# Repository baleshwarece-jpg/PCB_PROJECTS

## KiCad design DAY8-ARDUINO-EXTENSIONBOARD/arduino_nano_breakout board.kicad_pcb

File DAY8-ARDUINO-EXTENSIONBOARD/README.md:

# Arduino Nano Extension Board

### Compact GPIO breakout and prototyping platform for Arduino Nano development

---

## Overview

The Arduino Nano Extension Board is a simple yet highly practical PCB designed to transform the Arduino Nano into a more accessible and organized development platform. Rather than connecting sensors and modules directly to the Nano's tightly packed headers, this board expands every I/O pin into clearly labeled breakout connections, simplifying wiring, debugging, and rapid prototyping.

Designed in KiCad, the board emphasizes usability, signal accessibility, and clean PCB design practices while serving as a reusable hardware platform for embedded systems development.

---

## How It Works

The Arduino Nano plugs into a pair of female header sockets located at the center of the PCB. Every microcontroller pin is routed to dedicated breakout headers, allowing external peripherals to be connected without directly interacting with the Nano module.

Power rails distribute 5V and GND throughout the board, providing convenient access points for sensors, actuators, communication modules, and experimental circuits.

The extension board itself contains no active processing circuitry; instead, it functions as a structured interface layer between the Arduino Nano and external hardware, reducing wiring complexity and improving development efficiency.

---

## Bill of Materials

| Reference | Value          | Description                        | KiCad Symbol                | Footprint          |
| --------- | -------------- | ---------------------------------- | --------------------------- | ------------------ |
| U1        | Arduino Nano   | Microcontroller development module | MCU_Module:Arduino_Nano     | Pin Socket Headers |
| J1-Jn     | Pin Headers    | GPIO breakout connectors           | Connector_Generic:Conn_01xN | PinHeader_2.54mm   |
| C1        | 100 nF         | Power supply decoupling capacitor  | Device:C                    | C_0805             |
| H1-H4     | Mounting Holes | Mechanical mounting points         | Mechanical:MountingHole     | MountingHole_3.2mm |

Component count may vary depending on header configuration and optional features.

---

## Electrical Specifications

| Parameter                | Value                  |
| ------------------------ | ---------------------- |
| Operating Voltage        | 5 V                    |
| Logic Voltage            | 5 V                    |
| Input Power Source       | Arduino Nano USB / VIN |
| GPIO Access              | All Nano I/O Pins      |
| Analog Inputs            | A0 – A7                |
| Digital Inputs/Outputs   | D0 – D13               |
| Communication Interfaces | UART, SPI, I²C         |
| PCB Type                 | Two-Layer FR4          |
| Header Pitch             | 2.54 mm                |

---

## Schematic

Designed in KiCad 7.

Repository contents include:

* **Schematic:** `hardware/arduino_nano_extension.kicad_sch`
* **PCB Layout:** `hardware/arduino_nano_extension.kicad_pcb`
* **Gerber Files:** `hardware/gerbers/`
* **BOM:** `hardware/bom.csv`

The design passes ERC validation and follows standard Arduino Nano pin mapping conventions.

---

## Design Notes

### Why an Extension Board?

Although the Arduino Nano is one of the most widely used development boards, direct wiring often becomes difficult when multiple sensors, displays, and communication modules are connected simultaneously. An extension board provides a structured interface that improves accessibility and reduces connection errors.

### Header-Based Expansion

Every Nano pin is routed to dedicated headers, allowing peripherals to be connected without stacking wires directly onto the microcontroller module. This approach improves maintainability and makes debugging significantly easier.

### Power Distribution

Dedicated 5V and GND rails are distributed throughout the PCB to minimize wiring clutter during prototyping. Wide power traces were used to improve current handling and reduce voltage drop when powering multiple peripherals.

### Reusability

The board was designed as a general-purpose development platform rather than a project-specific shield. This allows the same PCB to be reused across robotics, IoT, automation, and embedded systems projects.

---

## Getting Started

1. Open the project files using KiCad 7 or later.
2. Review the schematic and verify ERC results.
3. Generate fabrication files or use the supplied Gerbers.
4. Assemble headers and passive components.
5. Install an Arduino Nano into the designated sockets.
6. Connect sensors, actuators, or communication modules through the breakout headers.
7. Upload firmware to the Nano and begin development.

No firmware modifications are required for board operation.

---

## License

Released under the CERN Open Hardware Licence Version 2 – Permissive (CERN-OHL-P).
You are free to study, modify, manufacture, and distribute this design in accordance with the license terms.

---

## References

* Arduino Nano Technical Documentation
* KiCad EDA Documentation
* Atmel ATmega328P Datasheet
* CERN Open Hardware Licence v2

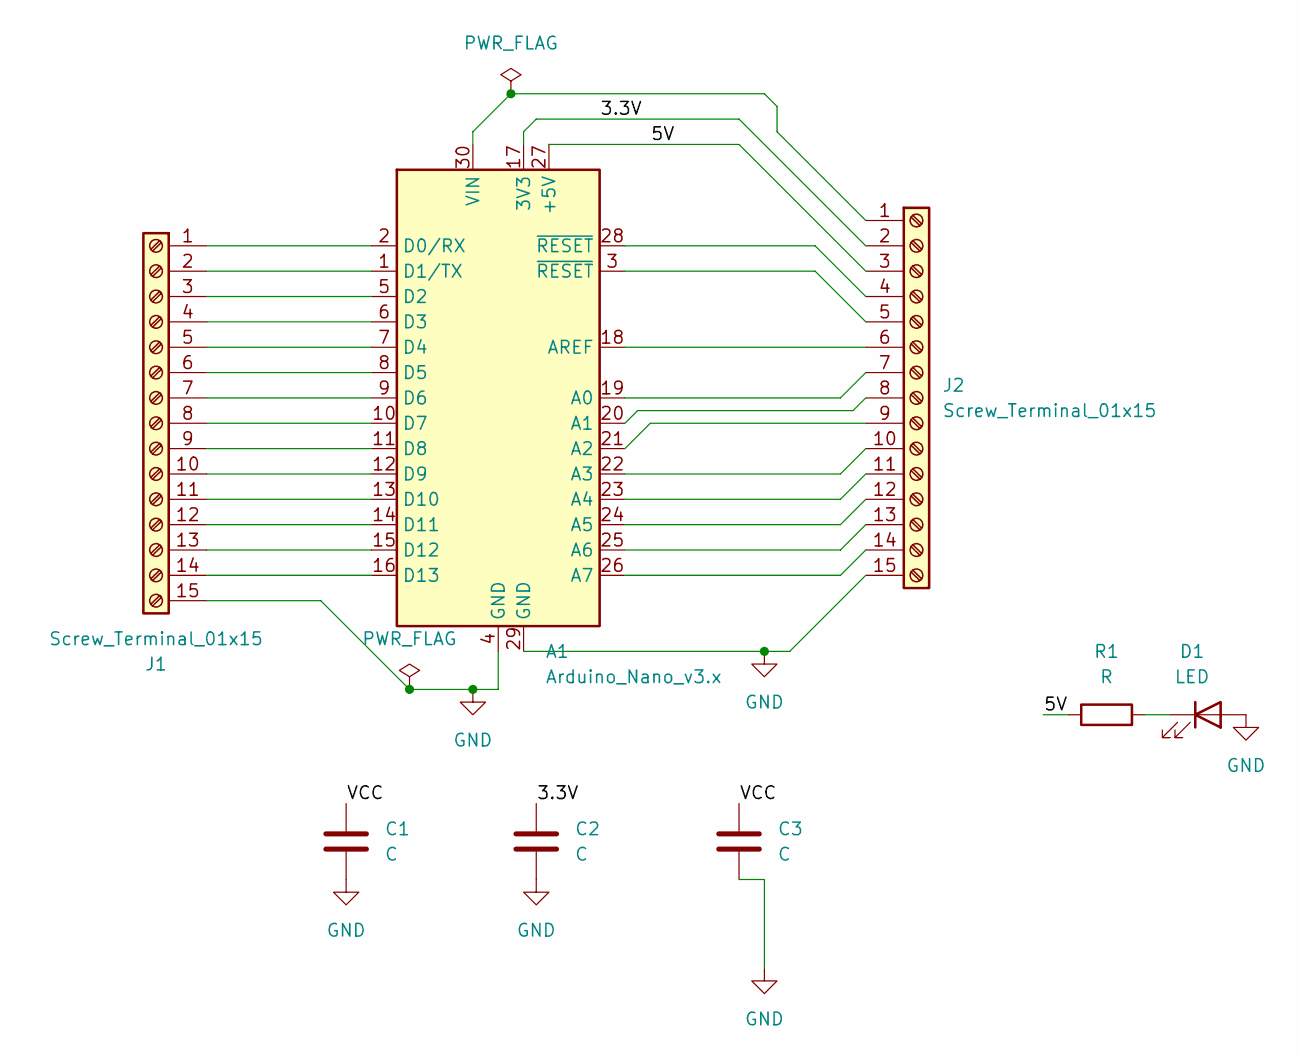
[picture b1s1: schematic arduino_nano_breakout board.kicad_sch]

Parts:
A1: Arduino_Nano_v3.x; Arduino_Nano
C1, C2, C3: C; C_0805_2012Metric
D1: LED; LED_D3.0mm
J1, J2: Screw_Terminal_01x15; TerminalBlock_MaiXu_MX126-5.0-15P_1x15_P5.00mm
R1: R; R_0805_2012Metric

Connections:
/3.3V: A1.17 (3V3), C2.1, J2.2
/5V: A1.27 (+5V), J2.3, R1.1
/VCC: C1.1, C3.1
GND: A1.4 (GND), A1.29 (GND), C1.2, C2.2, C3.2, D1.2 (A), J1.15, J2.15
unnamed: A1.19 (A0), J2.7
unnamed: A1.20 (A1), J2.8
unnamed: A1.21 (A2), J2.9
unnamed: A1.22 (A3), J2.10
unnamed: A1.23 (A4), J2.11
unnamed: A1.24 (A5), J2.12
unnamed: A1.25 (A6), J2.13
unnamed: A1.26 (A7), J2.14
unnamed: A1.18 (AREF), J2.6
unnamed: A1.2 (D0/RX), J1.1
unnamed: A1.1 (D1/TX), J1.2
unnamed: A1.5 (D2), J1.3
unnamed: A1.6 (D3), J1.4
unnamed: A1.7 (D4), J1.5
unnamed: A1.8 (D5), J1.6
unnamed: A1.9 (D6), J1.7
unnamed: A1.10 (D7), J1.8
unnamed: A1.11 (D8), J1.9
unnamed: A1.12 (D9), J1.10
unnamed: A1.13 (D10), J1.11
unnamed: A1.14 (D11), J1.12
unnamed: A1.15 (D12), J1.13
unnamed: A1.16 (D13), J1.14
unnamed: A1.30 (VIN), J2.1
unnamed: D1.1 (K), R1.2
unnamed: A1.28 (~RESET), J2.4
unnamed: A1.3 (~RESET), J2.5

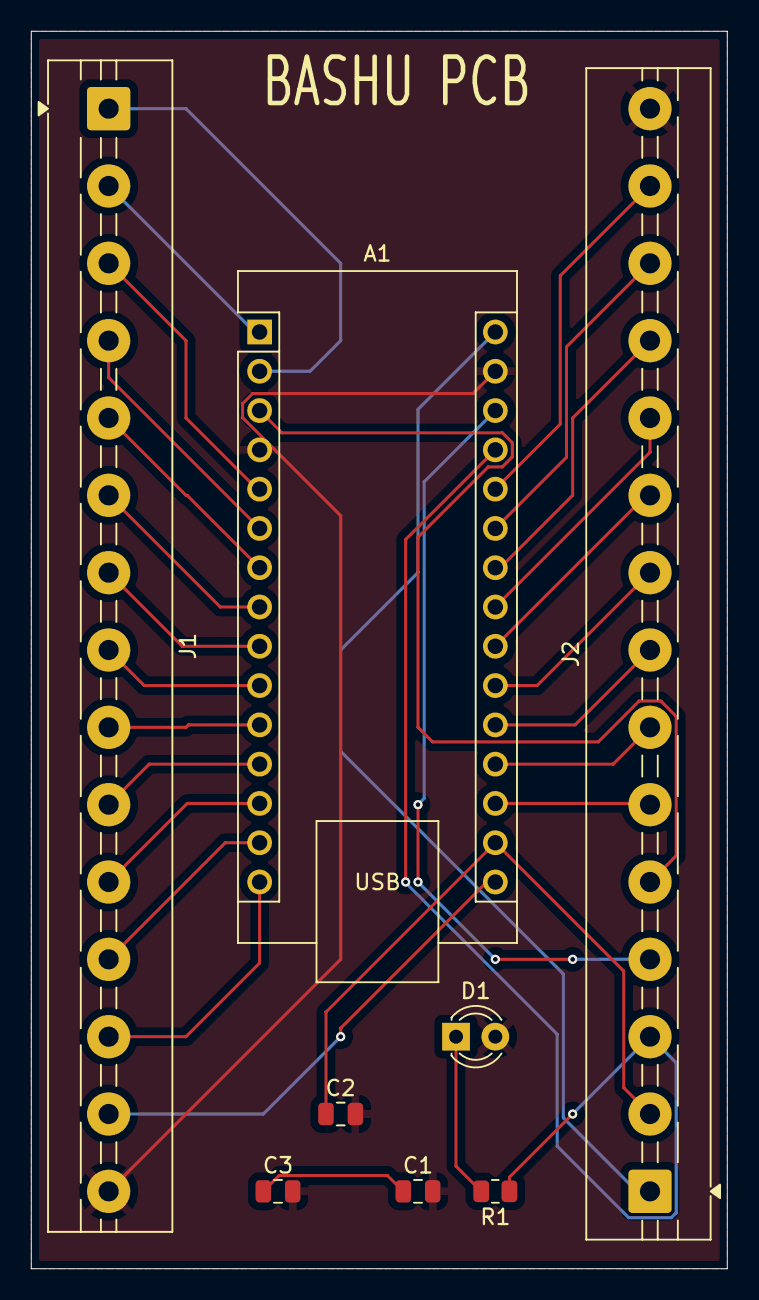
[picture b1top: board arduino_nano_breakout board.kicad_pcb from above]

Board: 2 copper layers, 45.0 x 80.0 mm, 8 parts (0 on the bottom side), 31 nets.

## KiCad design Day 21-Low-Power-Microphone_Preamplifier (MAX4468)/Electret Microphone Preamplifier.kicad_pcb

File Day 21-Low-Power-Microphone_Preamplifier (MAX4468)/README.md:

# Low-Power Microphone Preamplifier (MAX4468)
**Day 21 / 30 — 30-Day PCB Design Challenge**

A low-noise electret microphone preamplifier built around the MAX4468, designed for battery-powered audio sensing applications. Provides a biased, amplified, single-supply analog output suitable for direct connection to a microcontroller ADC.

---

## Overview

Electret condenser microphones output a very small AC signal (typically a few millivolts) on top of a DC bias point, and require both phantom power for the internal FET buffer and gain to bring the signal into a usable range for an ADC. The MAX4468 is a micropower operational amplifier specifically intended for this role — internally configured for unity-gain stable operation at low supply current, making it suitable for coin-cell or battery-powered listening applications such as sound level detection, voice activity sensing, or low-power audio triggering.

This board biases the electret element, sets adjustable gain via an external resistor network, and outputs a signal centered at VCC/2 so it can be sampled directly by a single-supply ADC without a negative rail.

---

## Specifications

| Parameter | Value |
|---|---|
| Supply Voltage | 2.4V – 5.5V |
| Supply Current | 24 µA typical (MAX4468 quiescent) |
| Microphone Type | Electret condenser, 2-terminal, FET buffered |
| Microphone Bias Voltage | ~2.0V (set by R1, supply dependent) |
| Gain (set) | 60 dB (configurable via R3/R4 ratio) |
| Output Bias Point | VCC / 2 |
| Output Type | Single-ended, AC-coupled audio on DC bias |
| Bandwidth | 20 Hz – 20 kHz (set by coupling capacitors) |
| PCB | 2-layer, 1 oz copper |

---

## Why a Dedicated Preamp Board

Electret microphones cannot be connected directly to a microcontroller ADC pin. The capsule requires a bias voltage to power its internal JFET source-follower, and its output swing is small enough that without gain, the signal sits below the ADC's effective resolution — a 5 mV signal into a 10-bit ADC with a 3.3V reference uses roughly 1.5 ADC codes of range, well below the noise floor of most microcontroller ADCs.

The MAX4468 was selected over a general-purpose op-amp specifically for its low quiescent current (24 µA), which matters in any design intended to run from a coin cell or small LiPo for extended periods — a standard op-amp drawing several hundred microamps to milliamps would dominate the power budget of an otherwise low-power sensing system. The MAX4468 is also unity-gain stable and rated for operation down to 2.4V, covering both 3.3V microcontroller rails and low-battery conditions.

---

## Signal Path

```
Electret Mic
     |
     v
  C1 (DC block, mic output side)  ----  R1 (bias resistor to VCC)
     |
     v
  R2 / C2 (input bias network to VCC/2)
     |
     v
  MAX4468 (gain set by R3, R4)
     |
     v
  C3 (output DC block)  ----  R5 / R6 (output bias network to VCC/2)
     |
     v
  Analog output to ADC
```

The microphone capsule is biased through R1 to VCC, supplying current to the internal JFET. C1 blocks the DC bias from reaching the amplifier input while passing the audio AC component. The non-inverting input of the MAX4468 is held at VCC/2 by a resistive divider (R2 network), which becomes the output bias point as well, since the device is configured for non-inverting gain referenced to that midpoint. The output is again AC-coupled through C3 so the final signal swings symmetrically around VCC/2 regardless of any small input offset.

---

## Schematic Overview

**MIC1 — Electret Condenser Microphone**
2-terminal type (output and ground, internal FET drain biased through R1). Positive terminal toward the PCB silkscreen marking faces away from the board when board-edge mounted, per typical capsule polarity convention — verify against the specific capsule datasheet, as terminal marking conventions vary by manufacturer.

**R1 — Microphone Bias Resistor (2.2 kOhm)**
Supplies bias current to the electret's internal FET. Value is a tradeoff: too low wastes current and loads the output; too high reduces available headroom and bias current to the capsule. 2.2 kOhm is a widely used value for standard electret capsules at 3.3V–5V supply, producing roughly 0.3–0.5 mA bias current depending on capsule characteristics.

**C1 — Input DC Block (1 µF)**
Couples the microphone's AC audio signal into the amplifier while blocking its DC bias point, preventing the mic bias from interacting with the amplifier's internal bias network.

**R2A, R2B — Input Bias Divider (100 kOhm each)**
Sets the non-inverting input, and therefore the output bias point, at VCC/2. High resistance value chosen to minimize loading on the AC signal path and to keep quiescent current contribution low, consistent with the MAX4468's micropower design intent.

**C2 — Bias Decoupling (1 µF)**
Across the lower leg of the R2 divider to GND, filtering noise on the VCC/2 reference node so bias noise does not appear as amplified hum or noise at the output.

**U1 — MAX4468**
Configured as a non-inverting amplifier. Gain set by R3 (feedback) and R4 (gain-setting resistor to the bias node) per the standard non-inverting gain equation, Gain = 1 + (R3/R4). With R3 = 100 kOhm and R4 = 1 kOhm, gain is approximately 101 (~40 dB); higher ratios increase gain further. Adjust R3/R4 ratio to match the expected microphone sensitivity and target ADC input range.

**C3 — Output DC Block (1 µF)**
Removes any output offset error before the signal reaches the output header, ensuring the downstream stage sees a clean VCC/2-centered swing if further AC coupling is needed, or can be omitted if the downstream ADC sampling stage expects a DC-biased input directly at VCC/2.

**C4 — Supply Decoupling (100 nF)**
Placed directly at the MAX4468 VCC pin, standard local decoupling practice for any analog IC.

---

## PCB Design Notes

- Designed in **KiCad 8**
- Microphone capsule placed at the board edge with a cutout or open area behind it to allow sound to reach the diaphragm without obstruction from the PCB substrate
- Analog ground poured separately from any digital/logic ground areas on the same board, joined at a single point near the supply input, to avoid digital switching noise coupling into the high-impedance microphone bias node
- R2 bias divider and C2 placed close to the MAX4468 input pins to minimize the loop area exposed to noise pickup, since this is the highest-impedance node in the circuit
- Feedback resistor R3 routed away from the input traces to avoid capacitive coupling between output and input, which can cause instability or peaking at high gain settings
- Output trace routed with a continuous ground plane reference underneath to reduce noise pickup over its length to the output header
- Component placement keeps the microphone, gain stage, and output header in a straight signal path with minimal trace crossing

---

## Getting Started

### Output Connection

| Pin | Signal | Description |
|---|---|---|
| VCC | Supply | 2.4V – 5.5V |
| GND | Ground | Common ground |
| OUT | Audio output | AC signal centered at VCC/2, connect to ADC pin |

### Reading the Output on a Microcontroller ADC

```cpp
const int MIC_PIN = A0;
const int SAMPLES = 100;

void setup() {
  Serial.begin(115200);
}

void loop() {
  int minVal = 1023;
  int maxVal = 0;

  for (int i = 0; i < SAMPLES; i++) {
    int val = analogRead(MIC_PIN);
    if (val < minVal) minVal = val;
    if (val > maxVal) maxVal = val;
    delayMicroseconds(100); // crude ~10 kHz sample window
  }

  int peakToPeak = maxVal - minVal;
  Serial.println(peakToPeak); // higher value = louder sound
}
```

This peak-to-peak envelope method gives a simple relative loudness reading without requiring an FFT, suitable for sound-triggered wake or threshold detection applications.

### Sound Level / Voice Activity Detection

For voice activity or clap detection, compare the peak-to-peak value above against a fixed or adaptive threshold. For frequency-domain analysis (e.g., distinguishing tones or speech bands), sample at a fixed rate (8–16 kHz is typical for voice-band analysis) and apply an FFT on the microcontroller or send raw samples to a host for processing.

---

## Gain Adjustment Reference

| R3 | R4 | Gain (V/V) | Gain (dB) | Typical Use |
|---|---|---|---|---|
| 100 kOhm | 10 kOhm | 11 | ~21 dB | Loud environments, close-talk |
| 100 kOhm | 4.7 kOhm | ~22 | ~27 dB | General ambient sound level |
| 100 kOhm | 1 kOhm | 101 | ~40 dB | Quiet room, moderate distance |
| 220 kOhm | 1 kOhm | 221 | ~47 dB | Whisper-level / distant pickup |

Higher gain settings amplify the MAX4468's own input-referred noise along with the signal. Select the lowest gain that brings the expected signal into the target ADC range rather than defaulting to maximum gain.

---

## BOM

| Reference | Part | Package | Value / Part No. |
|---|---|---|---|
| U1 | MAX4468 | SOT23-5 | Micropower op-amp |
| MIC1 | Electret condenser mic | SMD, 6mm | 2-terminal, FET buffered |
| C1, C3 | Ceramic / tantalum | 0603 | 1 µF |
| C2 | Ceramic | 0603 | 1 µF |
| C4 | Ceramic | 0402 | 100 nF |
| R1 | Resistor | 0402 | 2.2 kOhm |
| R2A, R2B | Resistor | 0402 | 100 kOhm |
| R3 | Resistor | 0402 | 100 kOhm (gain, adjustable per table) |
| R4 | Resistor | 0402 | 1 kOhm (gain, adjustable per table) |
| J1 | Pin header | 2.54 mm, 3-pin | VCC / GND / OUT |

---

## Common Issues

**No output signal / flat DC reading**
Verify R1 bias resistor is populated and the microphone capsule is oriented correctly — electret capsules are polarized and will not function if reversed. Confirm VCC is present at the MAX4468 supply pin.

**Output is clipped or distorted at moderate volume**
Gain set too high for the signal level and supply voltage. The output can only swing within the supply rails; at high gain, ordinary speech or ambient noise can drive the output into clipping at VCC or GND. Reduce gain per the gain adjustment table above.

**Persistent hum or noise on the output**
Check that C2 is populated and placed close to the bias divider, and that analog ground is not shared with a noisy digital ground plane on the same board. If powered from a switching supply, add additional decoupling or consider a separate linear regulator for the preamp supply rail.

**Output sits at a fixed rail instead of VCC/2**
Check the R2 bias divider resistors for correct value and placement; an open or incorrect resistor here will pull the bias point toward one rail instead of the midpoint, saturating the amplifier.

**Inconsistent sensitivity between board builds**
Electret capsules have wide manufacturing tolerance on sensitivity (often ±4 dB or more between units of the same part number). Calibrate gain or apply a software-side normalization step if absolute sound level accuracy matters across multiple boards.

## Repository Structure

```
MAX4468-Mic-Preamp/
├── hardware/
│   ├── Mic_Preamp.kicad_pro
│   ├── Mic_Preamp.kicad_sch
│   ├── Mic_Preamp.kicad_pcb
│   ├── gerbers/
│   │   └── Mic_Preamp_gerbers.zip
│   └── bom/
│       └── Mic_Preamp_BOM.csv
├── docs/
│   ├── schematic.pdf
│   ├── MAX4468_Datasheet.pdf
│   └── assembly_notes.md
└── README.md
```

---

## 30-Day PCB Challenge Progress

| Day | Board | Status |
|---|---|---|
| 19 | WS2812B RGB LED Strip Driver | Complete |
| 20 | Discrete MOSFET H-Bridge Motor Driver | Complete |
| **21** | **Low-Power Microphone Preamplifier (MAX4468)** | **Complete** |
| 22 | Coming soon | — |

---

## License

Hardware design files released under **CERN OHL v2 — Permissive**.

---

## References

- [MAX4468 Datasheet — Analog Devices (Maxim)](https://www.analog.com/media/en/technical-documentation/data-sheets/MAX4465-MAX4469.pdf)
- [Electret Microphone Biasing Application Notes — various manufacturer datasheets]
- [KiCad EDA](https://www.kicad.org/)

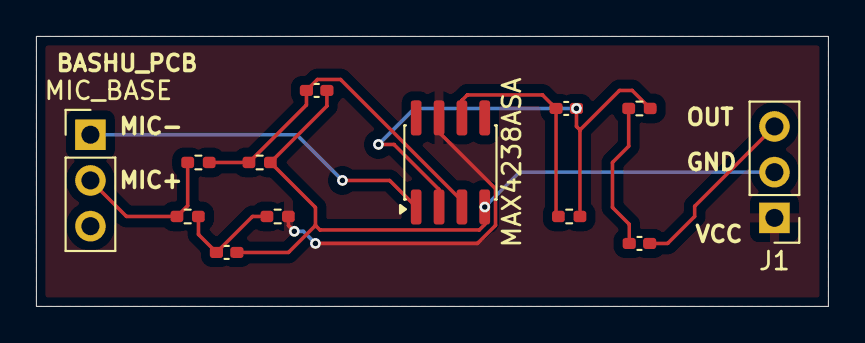
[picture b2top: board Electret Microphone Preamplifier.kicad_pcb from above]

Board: 2 copper layers, 44.0 x 15.0 mm, 13 parts (0 on the bottom side), 10 nets.

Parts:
C1: 10UF; C_0402_1005Metric_Pad0.74x0.62mm_HandSolder
C2: 0.01PF; C_0402_1005Metric_Pad0.74x0.62mm_HandSolder
C3: C; C_0402_1005Metric_Pad0.74x0.62mm_HandSolder
C4: 47PF; C_0402_1005Metric_Pad0.74x0.62mm_HandSolder
J1: Conn_01x03_Pin; PinHeader_1x03_P2.54mm_Vertical
MIC_BASE: Microphone_Crystal; PinHeader_1x03_P2.54mm_Vertical
R, R3: 100K; R_0402_1005Metric_Pad0.72x0.64mm_HandSolder
R1: 2.2K; R_0402_1005Metric_Pad0.72x0.64mm_HandSolder
R2: 1K; R_0402_1005Metric_Pad0.72x0.64mm_HandSolder
R5: R; R_0402_1005Metric_Pad0.72x0.64mm_HandSolder
R6: 200K; R_0402_1005Metric_Pad0.72x0.64mm_HandSolder
U1: MAX4238ASA; SOIC-8_3.9x4.9mm_P1.27mm

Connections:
/VCC: J1.1, R1.2, U1.7 (V+)
GND: C1.2, C2.2, J1.2, R.2, U1.4 (V-)
unnamed: C1.1, R1.1, R2.2
unnamed: C3.2, R5.1
unnamed: C4.2, R6.2, U1.6
unnamed: C3.1, J1.3
unnamed: MIC_BASE.2 (+), R2.1, R3.1
unnamed: MIC_BASE.1 (-), U1.1 (~SHDN)
unnamed: C2.1, R.1, R3.2, U1.3 (+)
unnamed: C4.1, R5.2, R6.1, U1.2 (-)

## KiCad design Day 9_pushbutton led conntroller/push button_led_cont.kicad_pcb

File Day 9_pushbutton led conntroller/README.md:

Pushbutton LED Controller
Simple hardware-based LED control circuit demonstrating switch interfacing, transistor driving, and debounce techniques
Overview

The Pushbutton LED Controller is a beginner-friendly PCB project designed to demonstrate how mechanical pushbuttons interact with electronic circuits to control loads. Instead of driving an LED directly from a switch, the design uses a transistor-based driver stage and a debounce network to improve switching reliability and circuit behavior.

This project introduces fundamental concepts used throughout embedded systems and digital electronics, including pull-up resistors, transistor switching, signal conditioning, and human-machine interfaces.

Designed in KiCad, the board serves as a practical learning platform for understanding how real-world button inputs are processed before being used by microcontrollers or digital logic systems.

How It Works

A pushbutton provides the user input for controlling the LED output. The button signal is stabilized using a resistor-capacitor debounce network that reduces unwanted switching caused by mechanical contact bounce.

When the button is pressed, the transistor receives a control signal through its base resistor and enters saturation mode. This allows current to flow through the LED and current-limiting resistor, illuminating the LED.

When the button is released, the pull-up resistor restores the input to its default state, turning the transistor off and extinguishing the LED.

The circuit demonstrates how low-current control signals can safely drive higher-current loads using a transistor interface.

Bill of Materials
Reference	Value	Description	KiCad Symbol	Footprint
SW1	Pushbutton	Momentary user input switch	Device:SW_Push	SW_Push
Q1	2N2222	NPN switching transistor	Device:Q_NPN_BCE	TO-92
R1	10 kΩ	Pull-up resistor	Device:R	R_0805
R2	1 kΩ	Base current limiting resistor	Device:R	R_0805
R3	220 Ω	LED current limiting resistor	Device:R	R_0805
C1	100 nF	Debounce capacitor	Device:C	C_0805
D1	LED	Status indicator LED	Device:LED	LED_D5.0mm
J1	Header	Power input connector	Connector_Generic	PinHeader_1x02
Electrical Specifications
Parameter	Value
Operating Voltage	5 V
Input Method	Momentary Pushbutton
Output Device	LED
Transistor Type	NPN BJT (2N2222)
LED Current	~10–15 mA
Debounce Capacitor	100 nF
PCB Type	Two-Layer FR4
Header Pitch	2.54 mm
Schematic

Designed using KiCad 7.

Repository contents include:

Schematic: hardware/pushbutton_led_controller.kicad_sch
PCB Layout: hardware/pushbutton_led_controller.kicad_pcb
Gerber Files: hardware/gerbers/
BOM: hardware/bom.csv

The design passes ERC validation and follows standard transistor switching practices.

Design Notes
Why Use a Transistor?

Although an LED can be driven directly through a pushbutton, introducing a transistor demonstrates how electronic systems use low-current control signals to switch loads efficiently. This principle forms the foundation of relay drivers, motor controllers, and microcontroller output stages.

Debounce Considerations

Mechanical switches do not produce perfectly clean transitions. During actuation, contacts physically bounce multiple times before settling. The RC debounce network helps suppress these unwanted transitions, improving signal stability.

Pull-Up Resistor Implementation

The pull-up resistor ensures the transistor remains in a known OFF state when the button is not pressed. Without this resistor, the transistor input could float, causing unpredictable LED behavior.

Educational Value

This project combines several essential electronics concepts into a single circuit:

BJT transistor operation
Current limiting
Pull-up resistor usage
Switch debouncing
Digital input conditioning
LED load control

These concepts are directly applicable to microcontroller-based designs and industrial control systems.

Getting Started
Open the project files using KiCad 7 or later.
Review the schematic and verify ERC results.
Generate fabrication files or use the supplied Gerbers.
Assemble all components according to the BOM.
Connect a regulated 5 V power source.
Press the pushbutton and observe LED operation.
Measure transistor voltages and currents for further analysis.

No firmware is required for operation.

license

Released under the CERN Open Hardware Licence Version 2 – Permissive (CERN-OHL-P).

You are free to study, modify, manufacture, and distribute this design in accordance with the license terms.

References
John Bardeen, Walter Brattain, and William Shockley — Transistor Fundamentals
Arduino Digital Input Design Practices
KiCad Documentation
2N2222 Transistor Datasheet
CERN Open Hardware Licence v2 (CERN-OHL-P)

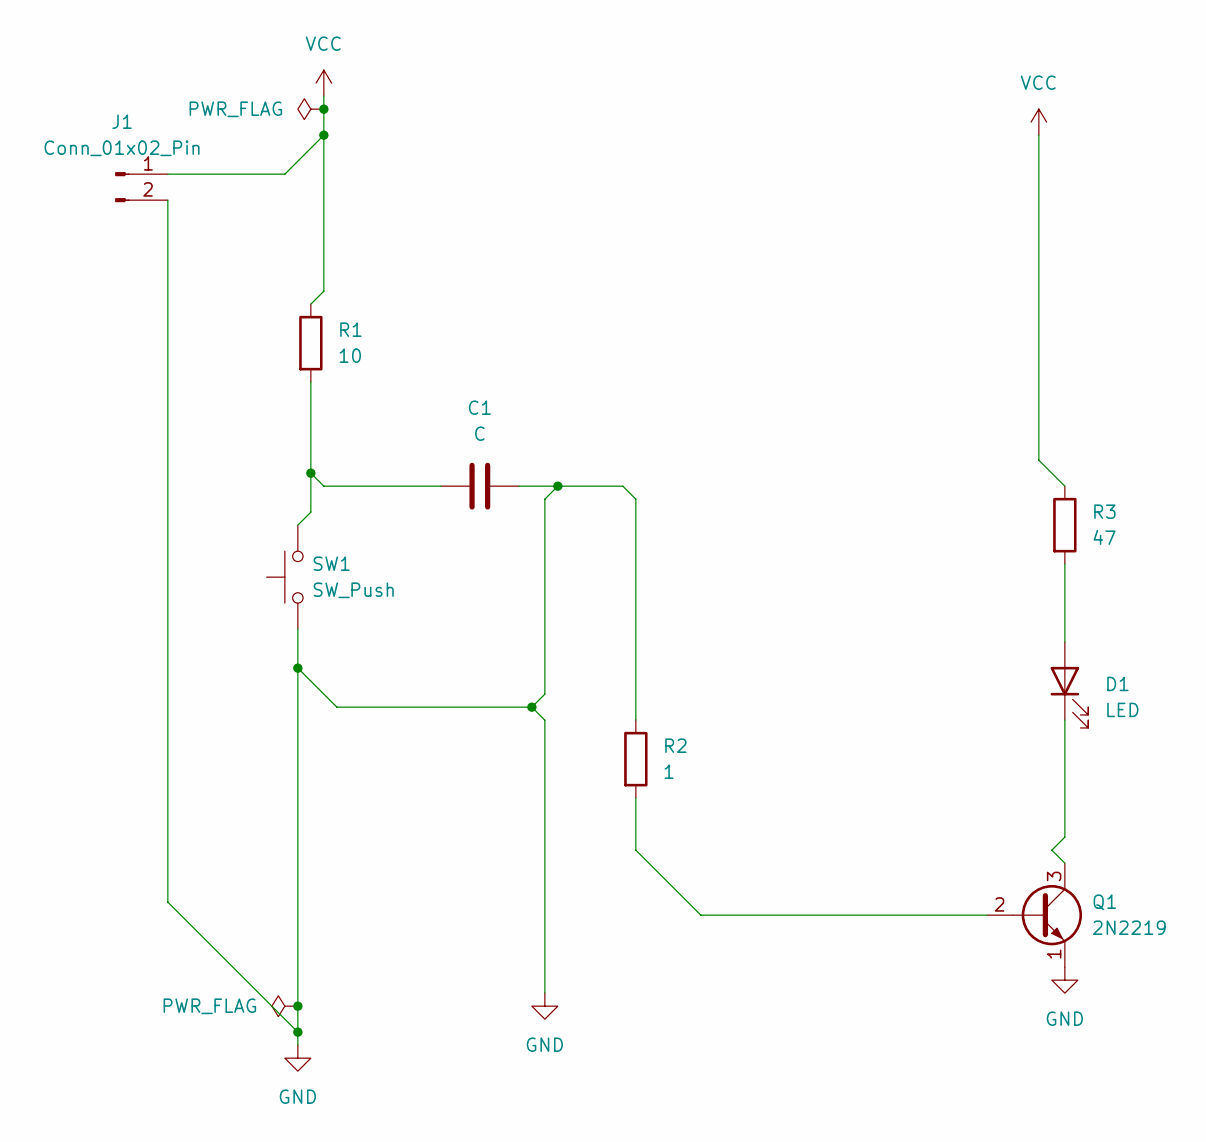
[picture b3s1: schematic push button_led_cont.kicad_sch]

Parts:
C1: C; C_Disc_D5.0mm_W2.5mm_P5.00mm
D1: LED; LED_D5.0mm
J1: Conn_01x02_Pin; TerminalBlock_MaiXu_MX126-5.0-02P_1x02_P5.00mm
Q1: 2N2219; TO-39-3
R1: 10; R_Axial_DIN0207_L6.3mm_D2.5mm_P10.16mm_Horizontal
R2: 1; R_Axial_DIN0207_L6.3mm_D2.5mm_P7.62mm_Horizontal
R3: 47; R_Axial_DIN0207_L6.3mm_D2.5mm_P10.16mm_Horizontal
SW1: SW_Push; SW_PUSH-12mm

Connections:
GND: C1.2, J1.2, Q1.1 (E), R2.1, SW1.1
unnamed: C1.1, R1.2, SW1.2
unnamed: D1.2 (A), R3.2
unnamed: D1.1 (K), Q1.3 (C)
unnamed: Q1.2 (B), R2.2
VCC: J1.1, R1.1, R3.1

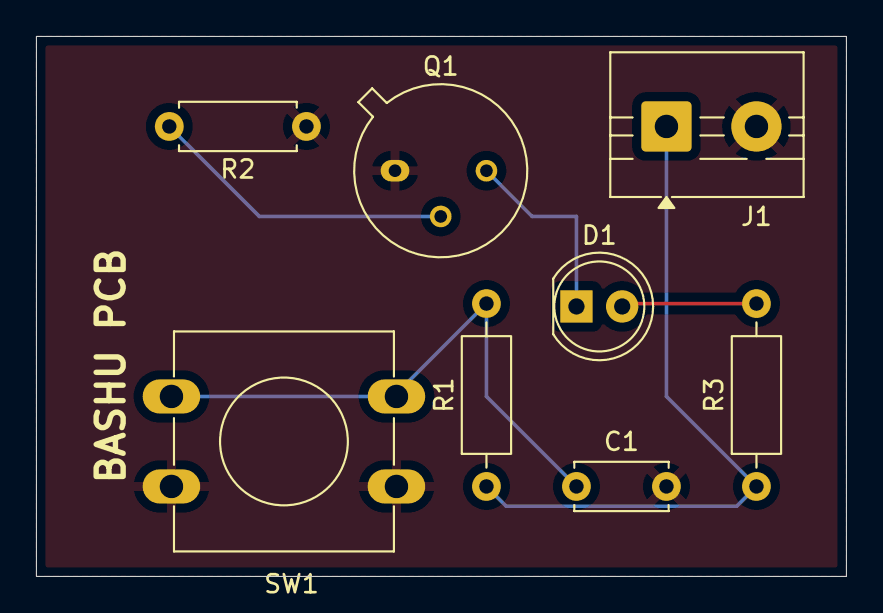
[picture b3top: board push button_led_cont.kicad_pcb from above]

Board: 2 copper layers, 45.0 x 30.0 mm, 8 parts (0 on the bottom side), 6 nets.

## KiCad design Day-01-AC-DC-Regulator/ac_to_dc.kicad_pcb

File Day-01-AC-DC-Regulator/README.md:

# ⚡ Day 1 - AC to DC Regulator PCB Design

## 🔧 Components Used
- resistor 
- Bridge Rectifier  
- Filter Capacitor  
- led
- screw terminals

## ⚙️ Key Functionalities
- AC to DC conversion  
- Ripple filtering  
- Voltage stabilization  

## 📘 Description
Designed a basic AC to DC regulator PCB focusing on clean layout and stable output.

## 🌍 Applications
- Power supply circuits  
- Embedded systems  

## 🚀 Future Improvements
- Protection circuits  
- Compact design  

## 📸 Preview

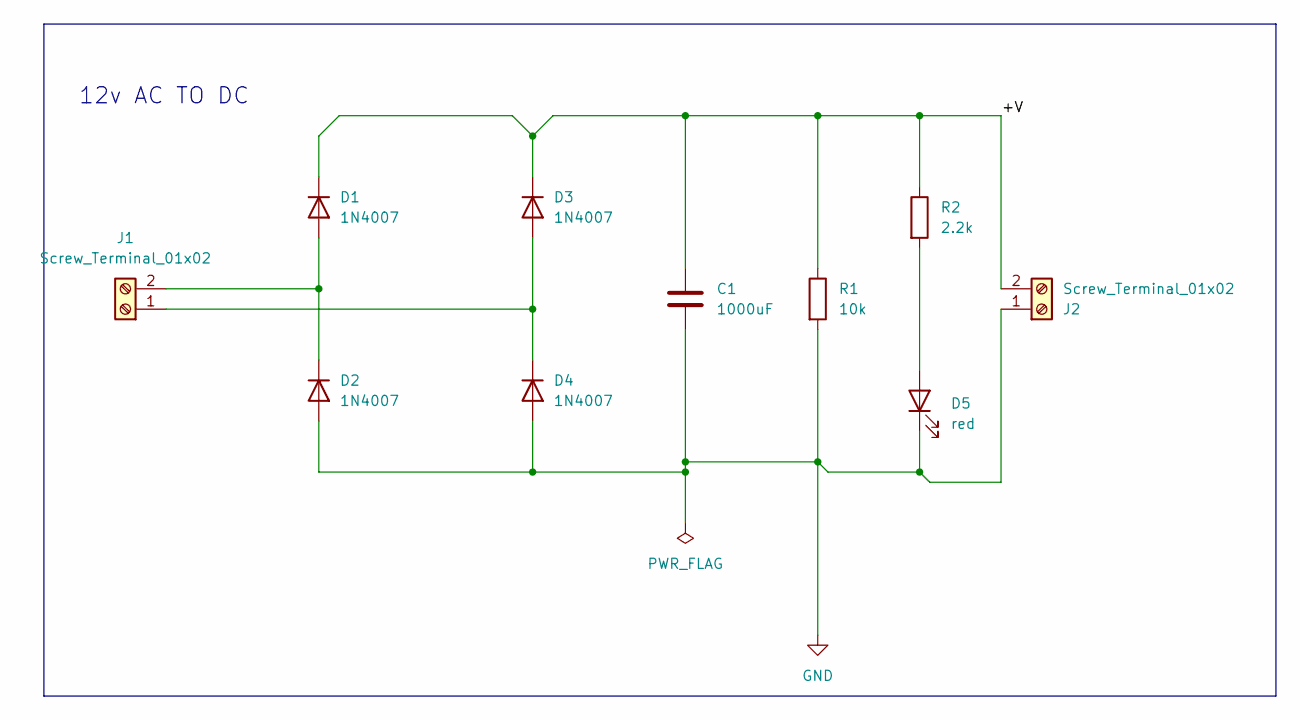
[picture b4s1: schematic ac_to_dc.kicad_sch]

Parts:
C1: 1000uF; C_Radial_D10.0mm_H12.5mm_P5.00mm
D1, D2, D3, D4: 1N4007; D_DO-41_SOD81_P10.16mm_Horizontal
D5: red; LED_D5.0mm
J1, J2: Screw_Terminal_01x02; TerminalBlock_MaiXu_MX126-5.0-02P_1x02_P5.00mm
R1: 10k; R_Axial_DIN0204_L3.6mm_D1.6mm_P7.62mm_Horizontal
R2: 2.2k; R_Axial_DIN0204_L3.6mm_D1.6mm_P7.62mm_Horizontal

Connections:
/+V: C1.1, D1.1 (K), D3.1 (K), J2.2, R1.1, R2.1
GND: C1.2, D2.2 (A), D4.2 (A), D5.1 (K), J2.1, R1.2
unnamed: D1.2 (A), D2.1 (K), J1.2
unnamed: D3.2 (A), D4.1 (K), J1.1
unnamed: D5.2 (A), R2.2

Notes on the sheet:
12v AC TO DC

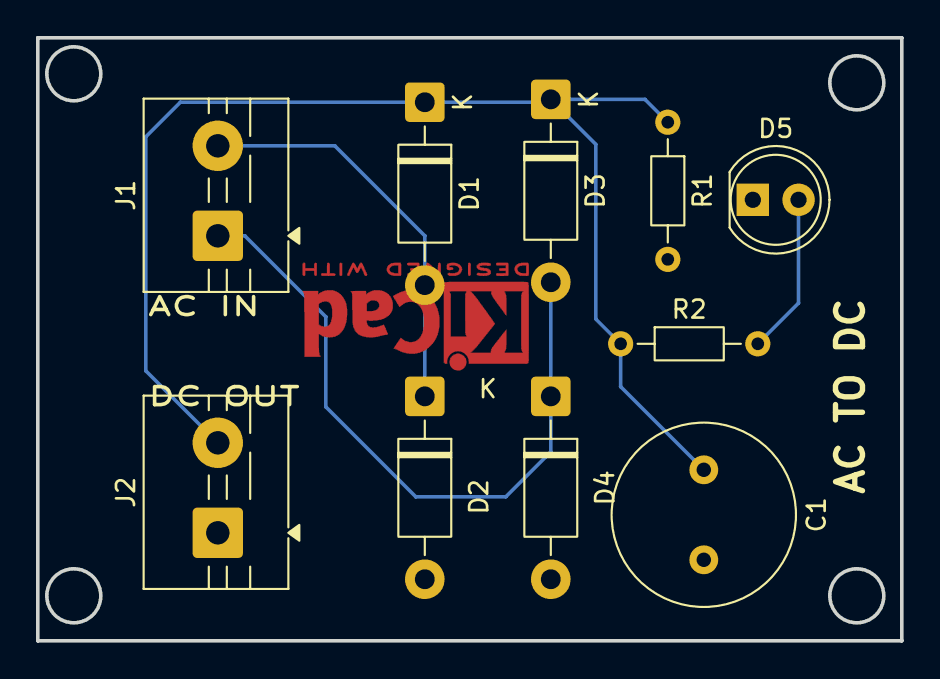
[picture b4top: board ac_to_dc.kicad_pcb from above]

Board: 2 copper layers, 48.0 x 33.5 mm, 10 parts (0 on the bottom side), 5 nets.

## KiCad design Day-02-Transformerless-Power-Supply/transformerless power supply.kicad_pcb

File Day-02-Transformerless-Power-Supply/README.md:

# 🔌 Transformerless Power Supply (5V) – Day 02 PCB Challenge

## 📌 Overview

Designed and analyzed a compact transformerless power supply circuit to convert AC mains to regulated 5V DC output using capacitive voltage dropping technique. This design focuses on low-cost, small form-factor applications.

---

## 🔧 Components Used

* Capacitor (X-rated for AC dropping)
* Resistors (current limiting & discharge)
* Zener Diode (voltage regulation)
* Bridge Rectifier
* Voltage Regulator (e.g., LM7805)
* Filter Capacitor
* Screw Terminals

---

## ⚙️ Key Functionalities

* Converts high-voltage AC to low-voltage DC
* Uses capacitive reactance instead of bulky transformer
* Provides regulated 5V output
* Compact and cost-efficient design

---

## 🧠 Working Principle

The circuit uses a **capacitor as a voltage dropper**, where capacitive reactance limits the current from AC mains. The reduced AC voltage is then rectified using a bridge rectifier and filtered. A Zener diode and voltage regulator ensure stable DC output.

---

## 📐 Design Considerations

* Capacitor value selection based on current requirement
* Proper discharge resistor for safety
* Heat dissipation in regulator
* Isolation limitations (non-isolated supply)

---

## 🚀 Applications

* Low-power embedded systems
* LED drivers
* IoT devices
* Small sensor circuits

---

## ⚠️ Safety Note

This is a **non-isolated circuit**, directly connected to AC mains. Proper insulation and handling precautions are mandatory.

---

## 🔮 Future Improvements

* Add fuse and MOV for protection
* Improve filtering for ripple reduction
* Thermal optimization of regulator
* Compact PCB layout design

---

## 📸 Project Visuals
## 📸 Schematic

## 🧩 PCB Layout

## 🔷 3D View

---

## 📅 Challenge Progress

Day 02 of **30 Days PCB Design Challenge**

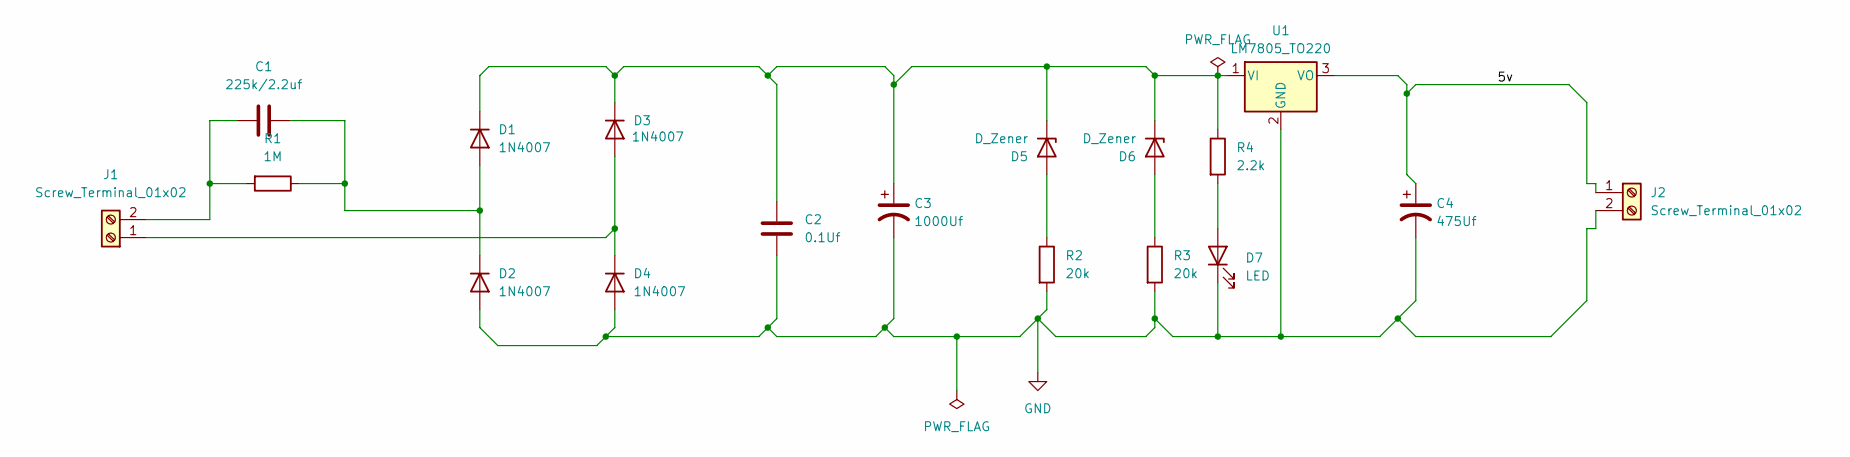
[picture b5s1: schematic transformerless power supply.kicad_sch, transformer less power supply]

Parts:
C1: 225k/2.2uf; C_Rect_L18.0mm_W6.0mm_P15.00mm_FKS3_FKP3
C2: 0.1Uf; C_Disc_D4.7mm_W2.5mm_P5.00mm
C3: 1000Uf; CP_Radial_D10.0mm_P5.00mm
C4: 475Uf; CP_Radial_D10.0mm_P3.80mm
D1, D2, D3, D4: 1N4007; D_DO-41_SOD81_P10.16mm_Horizontal
D5, D6: D_Zener; D_A-405_P7.62mm_Horizontal
D7: LED; LED_D5.0mm
J1, J2: Screw_Terminal_01x02; TerminalBlock_MaiXu_MX126-5.0-02P_1x02_P5.00mm
R1: 1M; R_Axial_DIN0207_L6.3mm_D2.5mm_P10.16mm_Horizontal
R2, R3: 20k; R_Axial_DIN0207_L6.3mm_D2.5mm_P10.16mm_Horizontal
R4: 2.2k; R_Axial_DIN0207_L6.3mm_D2.5mm_P10.16mm_Horizontal
U1: LM7805_TO220; TO-220-3_Vertical

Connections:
/5v: C4.1, J2.1, U1.3 (VO)
GND: C2.2, C3.2, C4.2, D2.2 (A), D4.2 (A), D7.1 (K), J2.2, R2.2, R3.2, U1.2 (GND)
unnamed: C1.1, D1.2 (A), D2.1 (K), R1.1
unnamed: C2.1, C3.1, D1.1 (K), D3.1 (K), D5.1 (K), D6.1 (K), R4.1, U1.1 (VI)
unnamed: D3.2 (A), D4.1 (K), J1.1
unnamed: D5.2 (A), R2.1
unnamed: D6.2 (A), R3.1
unnamed: D7.2 (A), R4.2
unnamed: C1.2, J1.2, R1.2

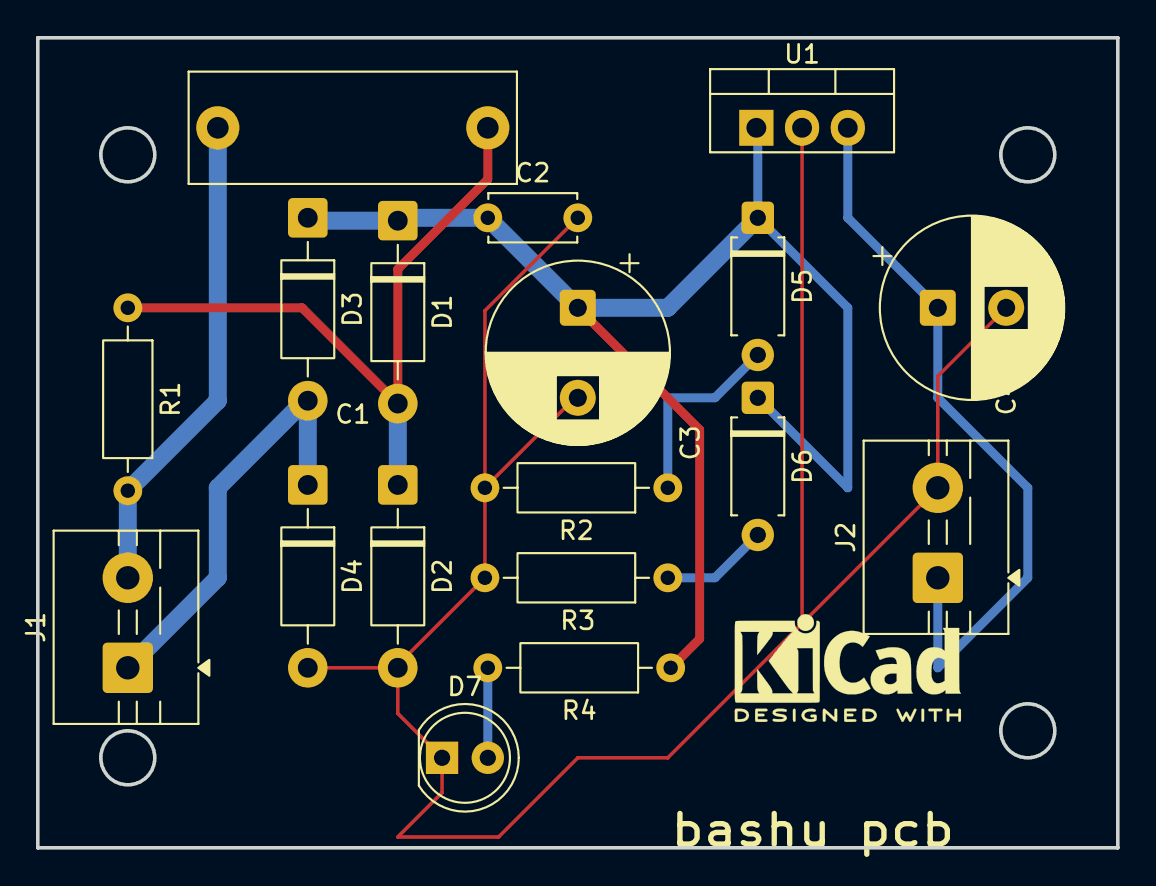
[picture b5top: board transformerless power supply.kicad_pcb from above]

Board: 2 copper layers, 60.0 x 45.0 mm, 18 parts (0 on the bottom side), 9 nets.

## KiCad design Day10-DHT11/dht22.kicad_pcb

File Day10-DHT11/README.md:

DHT11 Temperature & Humidity Sensor Interface
Environmental sensing platform for measuring ambient temperature and relative humidity using the DHT11 digital sensor
Overview

The DHT11 Temperature & Humidity Sensor Interface is a compact PCB designed to simplify environmental monitoring applications. Built around the popular DHT11 sensor, the board provides a reliable interface for measuring ambient temperature and relative humidity while demonstrating digital sensor integration techniques commonly used in embedded systems.

This project introduces sensor interfacing, digital communication, pull-up resistor implementation, power supply decoupling, and PCB layout considerations for low-speed digital peripherals.

Designed in KiCad, the board serves as a reusable module for weather stations, smart home systems, greenhouse monitoring, IoT devices, and environmental data logging applications.

How It Works

The DHT11 sensor contains an internal temperature sensing element, humidity sensing element, and a small microcontroller that processes the measurements.

When a host microcontroller requests data, the sensor transmits calibrated temperature and humidity values through a single-wire digital communication interface. A pull-up resistor maintains the data line in a known logic-high state when communication is idle.

A decoupling capacitor placed near the sensor helps stabilize the supply voltage and reduces noise that could affect measurement accuracy.

The board exposes power, ground, and data connections through standard headers, making integration with development platforms straightforward.

Bill of Materials
Reference	Value	Description	KiCad Symbol	Footprint
U1	DHT11	Temperature & humidity sensor	Sensor:DHT11	DHT11
R1	10 kΩ	Data line pull-up resistor	Device:R	R_0805
C1	100 nF	Power supply decoupling capacitor	Device:C	C_0805
J1	3-Pin Header	Power and data connector	Connector_Generic:Conn_01x03	PinHeader_1x03
H1-H2	Mounting Holes	Mechanical support	Mechanical:MountingHole	MountingHole_3.2mm
Electrical Specifications
Parameter	Value
Operating Voltage	3.3 V – 5 V
Typical Supply Voltage	5 V
Measured Parameters	Temperature & Humidity
Temperature Range	0°C to 50°C
Humidity Range	20% to 90% RH
Communication Interface	Single-Wire Digital
Pull-Up Resistor	10 kΩ
PCB Type	Two-Layer FR4
Header Pitch	2.54 mm
Schematic

Designed using KiCad 7.

Repository contents include:

Schematic: hardware/dht11_interface.kicad_sch
PCB Layout: hardware/dht11_interface.kicad_pcb
Gerber Files: hardware/gerbers/
BOM: hardware/bom.csv

The design passes ERC validation and follows the recommended DHT11 reference circuit.

Design Notes
Why Use the DHT11?

The DHT11 combines temperature sensing, humidity sensing, signal conditioning, and digital communication into a single package. This significantly reduces external circuitry while providing an easy introduction to environmental sensing.

Pull-Up Resistor Requirement

The DHT11 uses an open-drain style communication line that requires an external pull-up resistor. The 10 kΩ resistor ensures reliable logic transitions and stable communication between the sensor and host controller.

Power Supply Stability

Although the DHT11 has modest power requirements, a local decoupling capacitor was included to minimize supply noise and improve communication reliability.

Modular Design Philosophy

Rather than embedding the sensor directly into a larger system, this PCB functions as a reusable sensor module that can easily be integrated into future projects involving monitoring, automation, and IoT applications.

Learning Outcomes

This project provides hands-on experience with:

Digital sensor interfacing
Single-wire communication concepts
Pull-up resistor implementation
Sensor power conditioning
Environmental monitoring systems
Modular PCB design practices
Getting Started
Open the project files using KiCad 7 or later.
Review the schematic and verify ERC results.
Generate fabrication files or use the supplied Gerbers.
Assemble the PCB according to the BOM.
Connect power, ground, and data lines to a microcontroller.
Upload a DHT11 test program.
Read and display temperature and humidity measurements.

The hardware requires external firmware to request and process sensor data.

License

Released under the CERN Open Hardware Licence Version 2 – Permissive (CERN-OHL-P).

You are free to study, modify, manufacture, and distribute this design in accordance with the license terms.

References
DHT11 Digital Temperature and Humidity Sensor Datasheet
KiCad Documentation
Environmental Monitoring System Design Guides
Embedded Sensor Interfacing References
CERN Open Hardware Licence v2 (CERN-OHL-P)

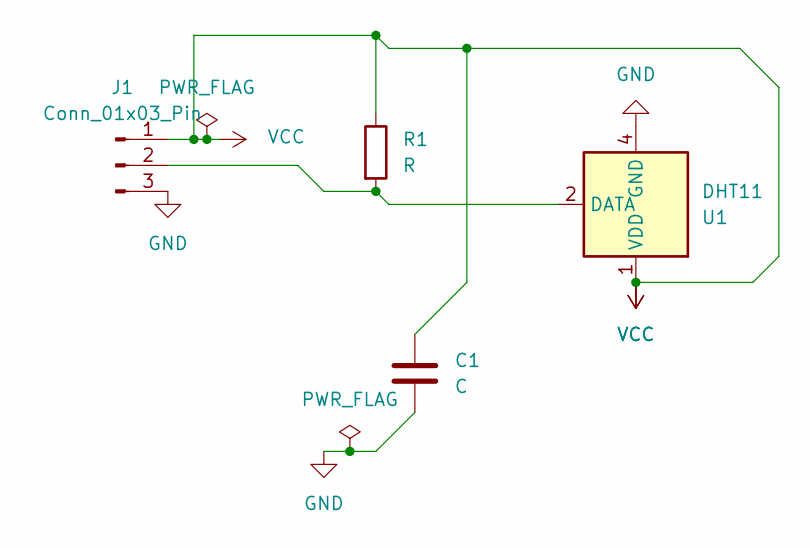
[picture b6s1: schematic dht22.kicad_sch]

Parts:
C1: C; C_Disc_D5.0mm_W2.5mm_P5.00mm
J1: Conn_01x03_Pin; TerminalBlock_MaiXu_MX126-5.0-03P_1x03_P5.00mm
R1: R; R_Axial_DIN0207_L6.3mm_D2.5mm_P10.16mm_Horizontal
U1: DHT11; Aosong_DHT11_5.5x12.0_P2.54mm

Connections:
GND: C1.2, J1.3, U1.4 (GND)
unnamed: J1.2, R1.2, U1.2 (DATA)
VCC: C1.1, J1.1, R1.1, U1.1 (VDD)

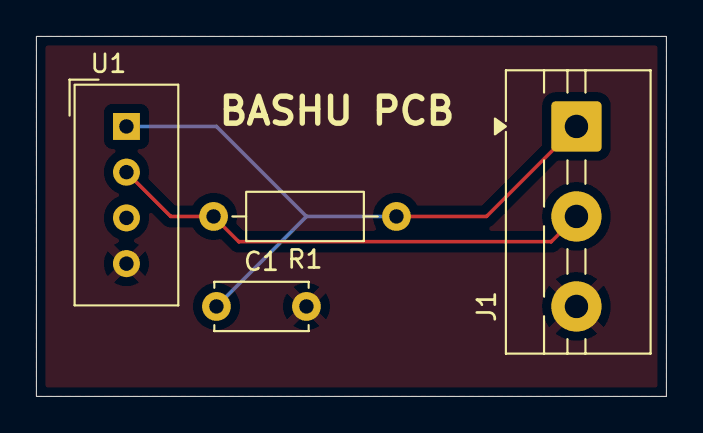
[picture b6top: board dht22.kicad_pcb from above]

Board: 2 copper layers, 35.0 x 20.0 mm, 4 parts (0 on the bottom side), 3 nets.

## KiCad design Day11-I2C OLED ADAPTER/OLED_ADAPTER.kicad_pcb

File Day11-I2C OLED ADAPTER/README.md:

I²C OLED Display Adapter
Compact interface board for connecting SSD1306-based OLED displays to microcontrollers using the I²C communication protocol
Overview

The I²C OLED Display Adapter is a simple yet practical PCB designed to provide a clean and reliable interface between microcontrollers and OLED displays. Built around the SSD1306-compatible I²C display ecosystem, the board exposes power and communication signals through clearly labeled headers, making display integration faster during prototyping and product development.

This project introduces digital communication buses, pull-up resistor networks, display interfacing techniques, and PCB design practices commonly used in embedded systems.

Designed in KiCad, the adapter serves as a reusable hardware module for IoT devices, sensor dashboards, robotics projects, portable instruments, and embedded user interfaces.

How It Works

The OLED display communicates with a host microcontroller using the I²C protocol, requiring only two signal lines:

SDA (Serial Data)
SCL (Serial Clock)

The adapter routes these signals from the display connector to standard breakout headers while providing dedicated power and ground connections.

Pull-up resistors on the SDA and SCL lines ensure proper bus operation by maintaining valid logic-high levels during communication. A local decoupling capacitor stabilizes the display supply voltage and helps reduce electrical noise.

Once connected, the microcontroller can send commands and graphical data to the OLED display, enabling text, icons, animations, and sensor information to be rendered on the screen.

Bill of Materials
Reference	Value	Description	KiCad Symbol	Footprint
J1	OLED Connector	SSD1306 OLED display header	Connector_Generic:Conn_01x04	PinHeader_1x04
R1	4.7 kΩ	SDA pull-up resistor	Device:R	R_0805
R2	4.7 kΩ	SCL pull-up resistor	Device:R	R_0805
C1	100 nF	Power supply decoupling capacitor	Device:C	C_0805
J2	I²C Breakout Header	Microcontroller interface connector	Connector_Generic:Conn_01x04	PinHeader_1x04
H1-H2	Mounting Holes	Mechanical support	Mechanical:MountingHole	MountingHole_3.2mm
Electrical Specifications
Parameter	Value
Operating Voltage	3.3 V – 5 V
Communication Protocol	I²C
I²C Signals	SDA, SCL
Pull-Up Resistors	4.7 kΩ
Typical Display Controller	SSD1306
Display Support	0.96" / 1.3" OLED Modules
PCB Type	Two-Layer FR4
Header Pitch	2.54 mm
Schematic

Designed using KiCad 7.

Repository contents include:

Schematic: hardware/i2c_oled_adapter.kicad_sch
PCB Layout: hardware/i2c_oled_adapter.kicad_pcb
Gerber Files: hardware/gerbers/
BOM: hardware/bom.csv

The design passes ERC validation and follows standard I²C hardware design practices.

Design Notes
Why Use I²C?

I²C significantly reduces wiring complexity compared to parallel display interfaces. With only two communication lines, multiple peripherals can share the same bus, making it ideal for compact embedded systems.

Pull-Up Resistor Selection

I²C devices use open-drain outputs, meaning the bus requires external pull-up resistors to generate logic-high levels. The 4.7 kΩ resistors provide a good balance between power consumption and communication reliability for short PCB traces.

Signal Integrity Considerations

Although I²C operates at relatively low speeds, proper routing and local power decoupling improve communication stability and reduce susceptibility to electrical noise.

Modular Hardware Design

Separating the display interface into a dedicated adapter board improves system flexibility. Different microcontrollers can reuse the same display hardware without requiring redesign of the display section.

Learning Outcomes

This project provides practical experience with:

I²C communication fundamentals
Pull-up resistor implementation
OLED display interfacing
Embedded user interface hardware
Power supply decoupling
Modular PCB architecture
Getting Started
Open the project files using KiCad 7 or later.
Review the schematic and verify ERC results.
Generate fabrication files or use the supplied Gerbers.
Assemble the PCB according to the BOM.
Connect an SSD1306-compatible OLED display.
Connect SDA, SCL, VCC, and GND to a microcontroller.
Upload a display test program and verify communication.

The adapter requires external firmware to drive the OLED display.

License

Released under the CERN Open Hardware Licence Version 2 – Permissive (CERN-OHL-P).

You are free to study, modify, manufacture, and distribute this design in accordance with the license terms.

References
SSD1306 OLED Display Controller Datasheet
I²C Bus Specification Documentation
KiCad Documentation
Embedded Display Interface Design Guides
CERN Open Hardware Licence v2 (CERN-OHL-P)

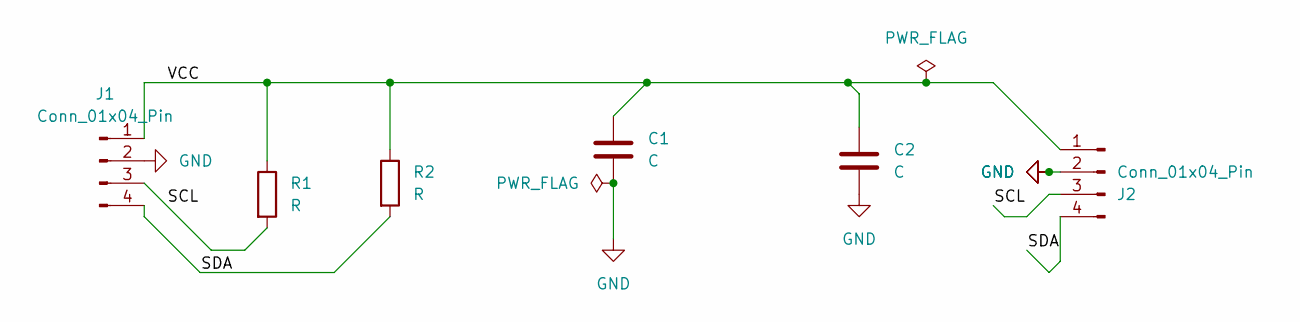
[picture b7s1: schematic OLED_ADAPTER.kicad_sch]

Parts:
C1, C2: C; C_0805_2012Metric
J1, J2: Conn_01x04_Pin; TerminalBlock_MaiXu_MX126-5.0-04P_1x04_P5.00mm
R1, R2: R; R_0805_2012Metric_Pad1.20x1.40mm_HandSolder

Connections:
/SCL: J1.3, J2.3, R1.2
/SDA: J1.4, J2.4, R2.2
/VCC: C1.1, C2.1, J1.1, J2.1, R1.1, R2.1
GND: C1.2, C2.2, J1.2, J2.2

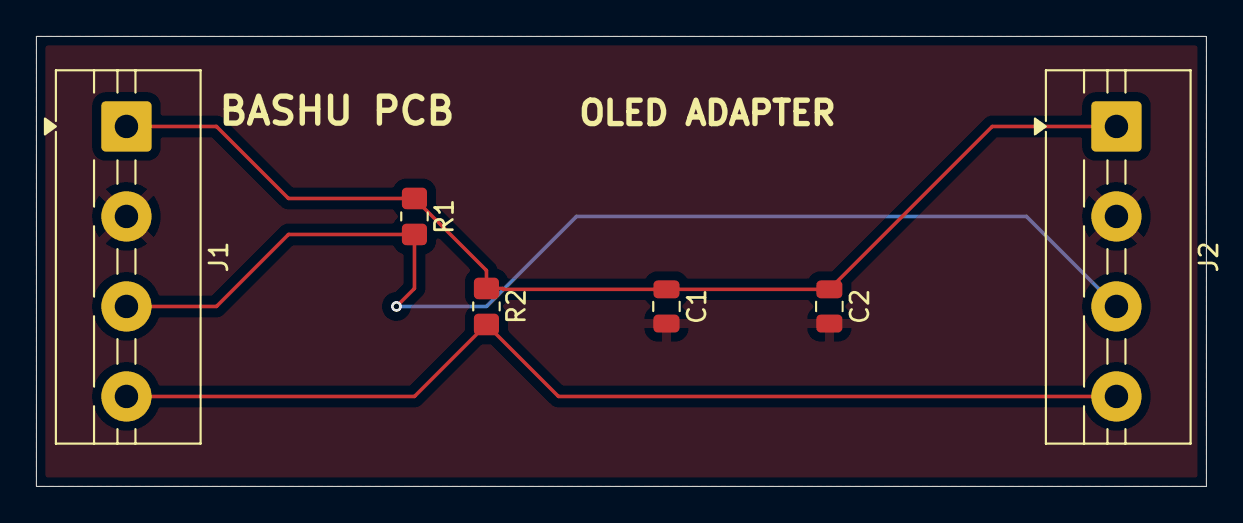
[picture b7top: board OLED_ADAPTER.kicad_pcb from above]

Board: 2 copper layers, 65.0 x 25.0 mm, 6 parts (0 on the bottom side), 4 nets.
